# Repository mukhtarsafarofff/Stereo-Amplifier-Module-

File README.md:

(ENG) I have used a single IC stereo amplifier which is based on TDA7377. This TDA7377 can be configured in different wattage modes. Here I am using  Because it has 4 channel max output which can give 6w per channel on a 4ohm load. I am using the stereo + bridge configuration. Which makes a 2.1 channel amplifier (1 channel for subwoofer and two for speakers)1 channel for subwoofer and other one for speaker. TDA IC can work with single 12volt power supply. And due to class AB operation need a very little heat sink. I can use this IC in bridge mode or in simple mode. The standby is kept on high for the amplifying action of the TDA7377. I need 3 inputs to run this amplifier, either I can use a preamp or direct 3 channel input can be given. I have used 20x20mm heatsink with this IC. So that no thermal damage will be there. I am using this circuit with constant 12v power supply, it demands a maximum current of 2Amperes. So it is recommended to pair the amplifier with at least 2A power source.The performance is quite good and  it is loud enough for a single room home theatre system. I have used 20x20mm heatsink with this IC. So that no thermal damage will be there. I am using this circuit with constant 12v power supply, it demands a maximum current of 2Amperes. So it is recommended to pair the amplifier with at least 2A power source. The performance is quite good and it is loud enough for a single room home theatre system.  

(
Ich kann diesen IC im Brückenmodus oder im einfachen Modus verwenden.Dieser TDA7377 kann in verschiedenen Leistungsmodi konfiguriert werden. Hier verwende ich einen Kanal für den Subwoofer und den anderen für den Lautsprecher. Der TDA-IC kann mit einer einzigen 12-Volt-Stromversorgungbetrieben werden. Aufgrund der Klasse-AB-Betriebsweise benötigt er nur einen sehr kleinen Kühlkörper. Da er eine maximale Ausgangsleistung von 4 Kanälen bietet, die bei einer 4-Ohm-Last jeweils 6 W pro Kanal liefern können, nutze ich die Stereo- + Brücken-Konfiguration, was einen 2.1-Kanal-Verstärker ergibt (1 Kanal für den Subwoofer und zwei für die Lautsprecher).  Der Standby wird auf hoch gehalten, um die Verstärkungsfunktion des TDA7377 zu ermöglichen.  Ich benötige 3 Eingänge, um diesen Verstärker zu betreiben; entweder kann ich einen Vorverstärker verwenden oder direkt einen 3-Kanal-Eingang anschließen. Ich habe einen 20x20 mm Kühlkörper mit diesem IC verwendet, um thermische Schäden zu vermeiden.  Ich betreibe diese Schaltung mit einer konstanten 12-V-Stromversorgung, die einen maximalen Strom von 2 Ampere erfordert.  Daher wird empfohlen, den Verstärker mit einer mindestens 2A-Stromquelle zu koppeln. Die Leistung ist ziemlich gut und laut genug für ein einzelnes Zimmer-Heimkinosystem.

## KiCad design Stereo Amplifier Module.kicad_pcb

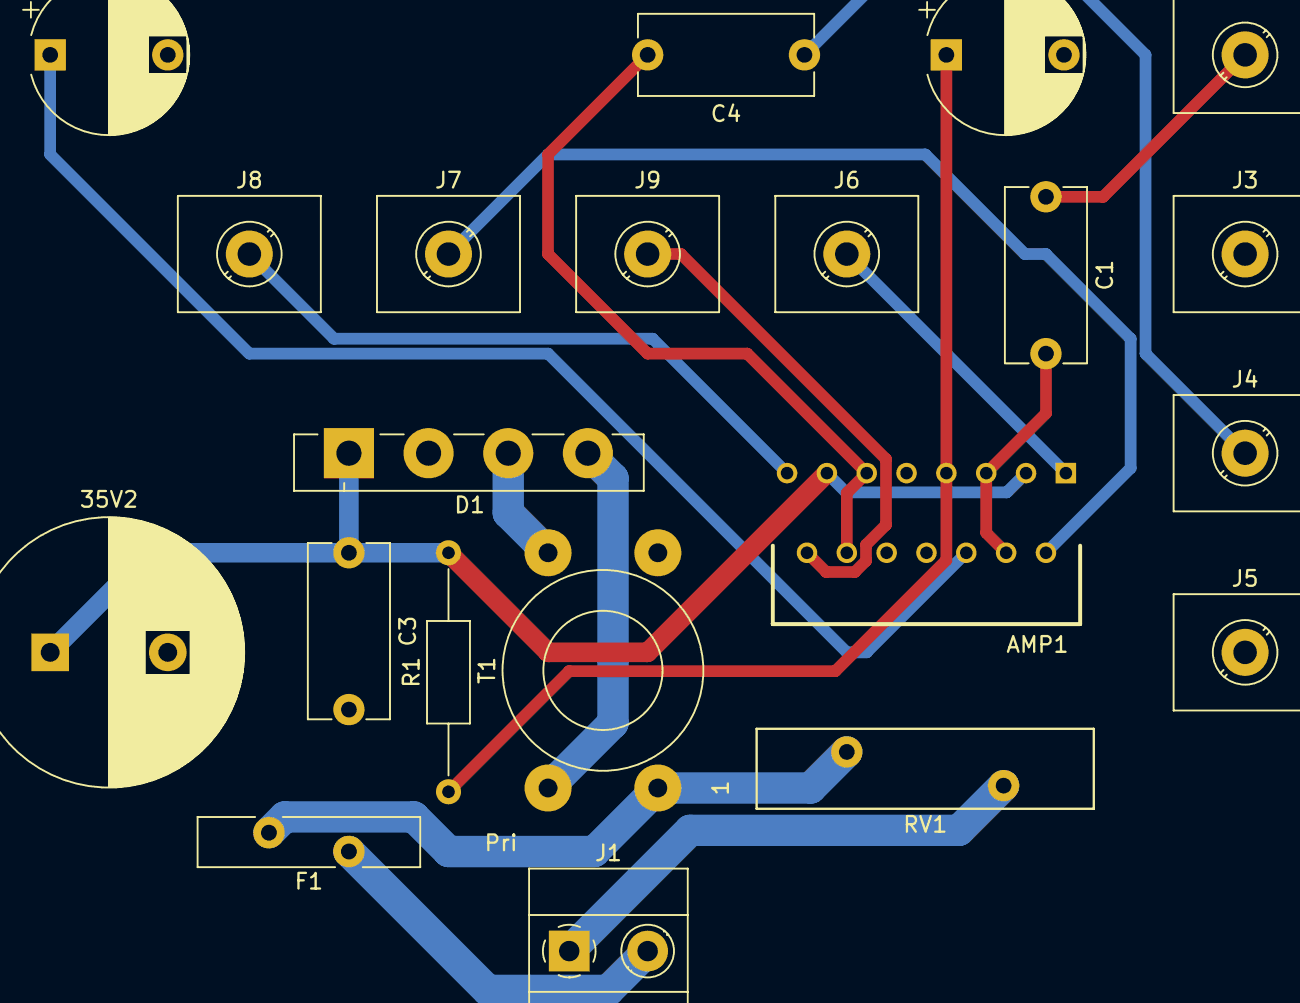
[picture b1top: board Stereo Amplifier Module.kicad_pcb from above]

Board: 2 copper layers, 21 parts (0 on the bottom side), 17 nets.

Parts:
35V1, 35V3: 47uF; CP_Radial_D10.0mm_P7.50mm
35V2: 3300uF; CP_Radial_D17.0mm_P7.50mm
AMP1: TDA7377; AMP_TDA7377
C1, C4: 330nF; C_Disc_D11.0mm_W5.0mm_P10.00mm
C3: 220pF; C_Disc_D11.0mm_W5.0mm_P10.00mm
D1: Bridge D; Diode_Bridge_Vishay_GBU
F1: Fuse; Fuse_Bourns_MF-RHT750
J1: AC 230V 50Hz; TerminalBlock_Phoenix_MKDS-1,5-2_1x02_P5.00mm_Horizontal
J2: IN Right2; TerminalBlock_MetzConnect_360271_1x01_Horizontal_ScrewM3.0_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
J3: IN Right1; TerminalBlock_MetzConnect_360271_1x01_Horizontal_ScrewM3.0_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
J4: IN Left1; TerminalBlock_MetzConnect_360271_1x01_Horizontal_ScrewM3.0_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
J5: IN Left2; TerminalBlock_MetzConnect_360271_1x01_Horizontal_ScrewM3.0_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
J6: OUT Right2; TerminalBlock_MetzConnect_360271_1x01_Horizontal_ScrewM3.0_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
J7: OUT Right1; TerminalBlock_MetzConnect_360271_1x01_Horizontal_ScrewM3.0_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
J8: OUT Left1; TerminalBlock_MetzConnect_360271_1x01_Horizontal_ScrewM3.0_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
J9: OUT Left2; TerminalBlock_MetzConnect_360271_1x01_Horizontal_ScrewM3.0_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
R1: 10K; R_Axial_DIN0207_L6.3mm_D2.5mm_P15.24mm_Horizontal
RV1: 250VAC; RV_Disc_D21.5mm_W5.1mm_P10mm
T1: 230V-9V; Transformer_Toroid_Horizontal_D12.5mm_Amidon-T44

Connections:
+12V: 35V2.1, AMP1.3 (VCC1), AMP1.13 (VCC2), C3.1, D1.1 (+), R1.2
CONN: 35V3.1, AMP1.7 (STANDBY), R1.1
Earth: 35V1.2, 35V2.2, 35V3.2, AMP1.8 (PWGND), AMP1.9 (SGND), C3.2, D1.2 (-), J3.1, J5.1
unnamed: AMP1.4 (IN1), AMP1.5 (IN2), C1.2
unnamed: AMP1.11 (IN4), AMP1.12 (IN3), C4.2
unnamed: AMP1.1 (OUT1), J6.1
unnamed: AMP1.2 (OUT2), J7.1
unnamed: AMP1.15 (OUT3), J8.1
unnamed: AMP1.14 (OUT4), J9.1
unnamed: 35V1.1, AMP1.6 (SVR)
unnamed: J1.1, RV1.2
unnamed: F1.1, J1.2
unnamed: C1.1, J2.1
unnamed: C4.1, J4.1
unnamed: F1.2, RV1.1, T1.1 (AA)
unnamed: D1.4, T1.3 (SA)
unnamed: D1.3, T1.4 (SB)

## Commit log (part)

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2024-04-06 Stereo Amplifier Module is accomplished
